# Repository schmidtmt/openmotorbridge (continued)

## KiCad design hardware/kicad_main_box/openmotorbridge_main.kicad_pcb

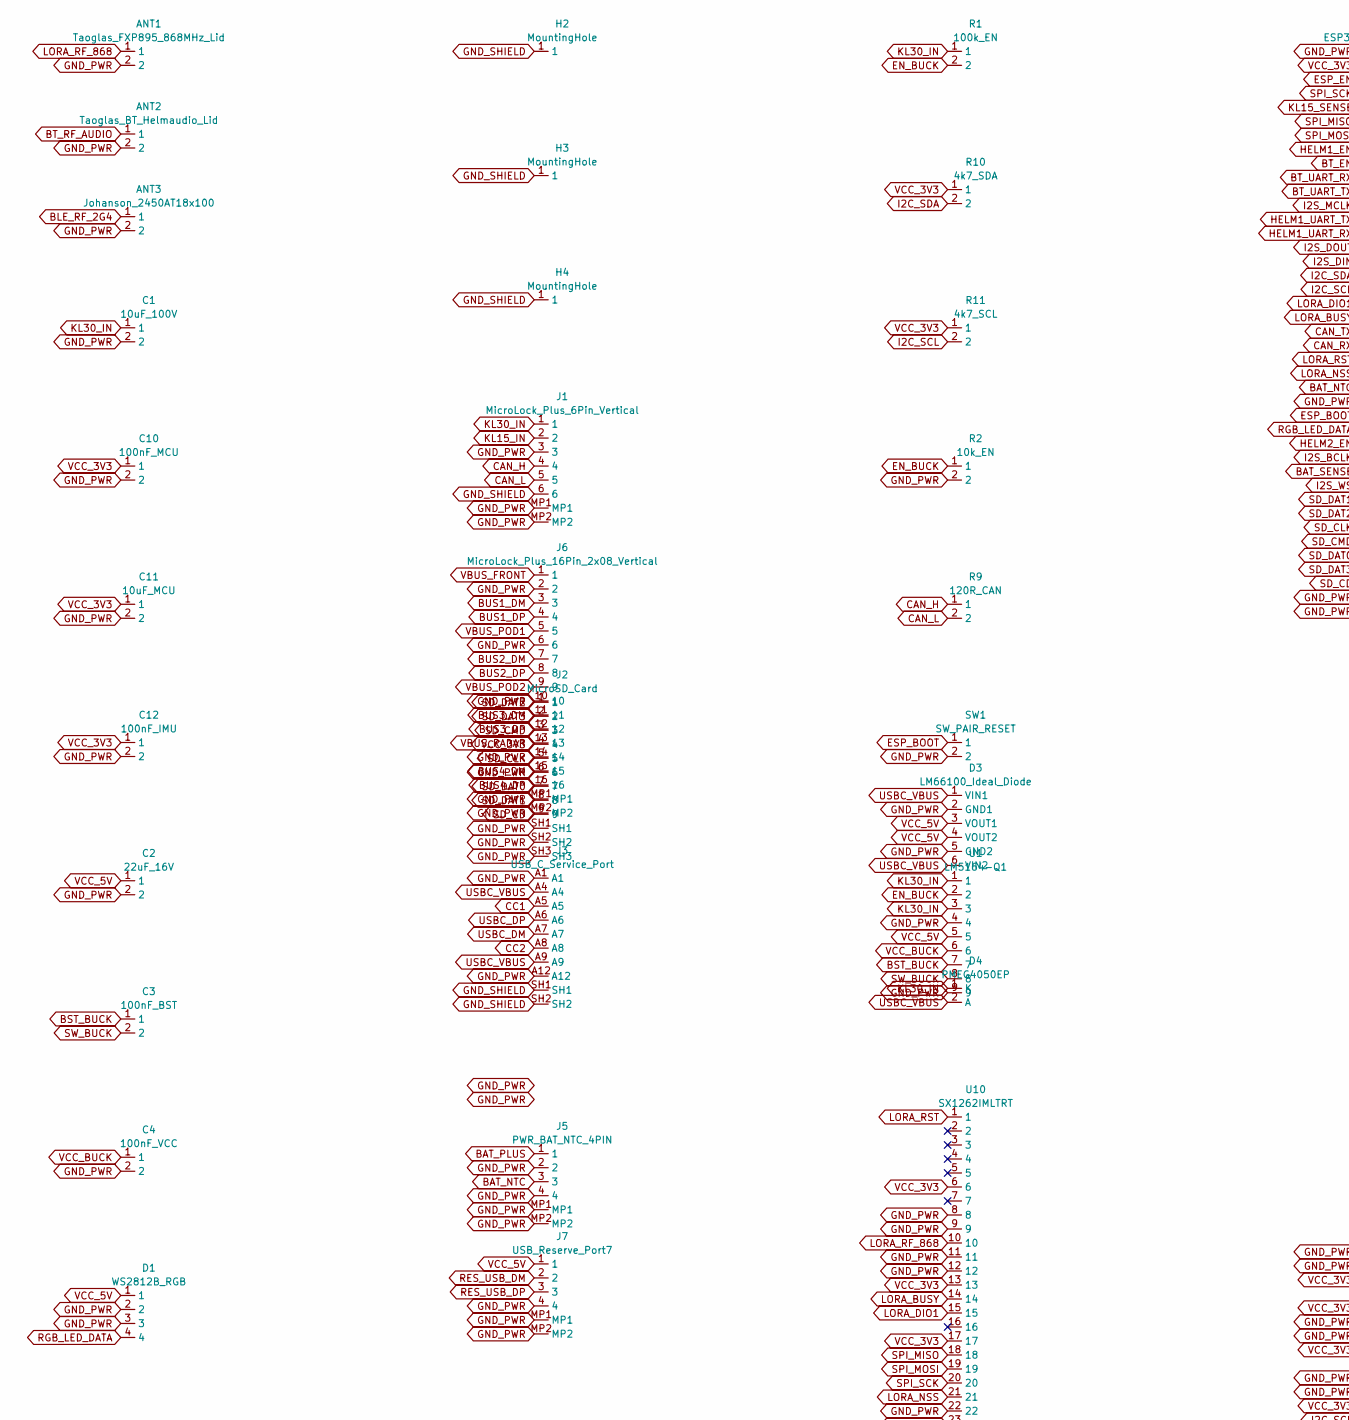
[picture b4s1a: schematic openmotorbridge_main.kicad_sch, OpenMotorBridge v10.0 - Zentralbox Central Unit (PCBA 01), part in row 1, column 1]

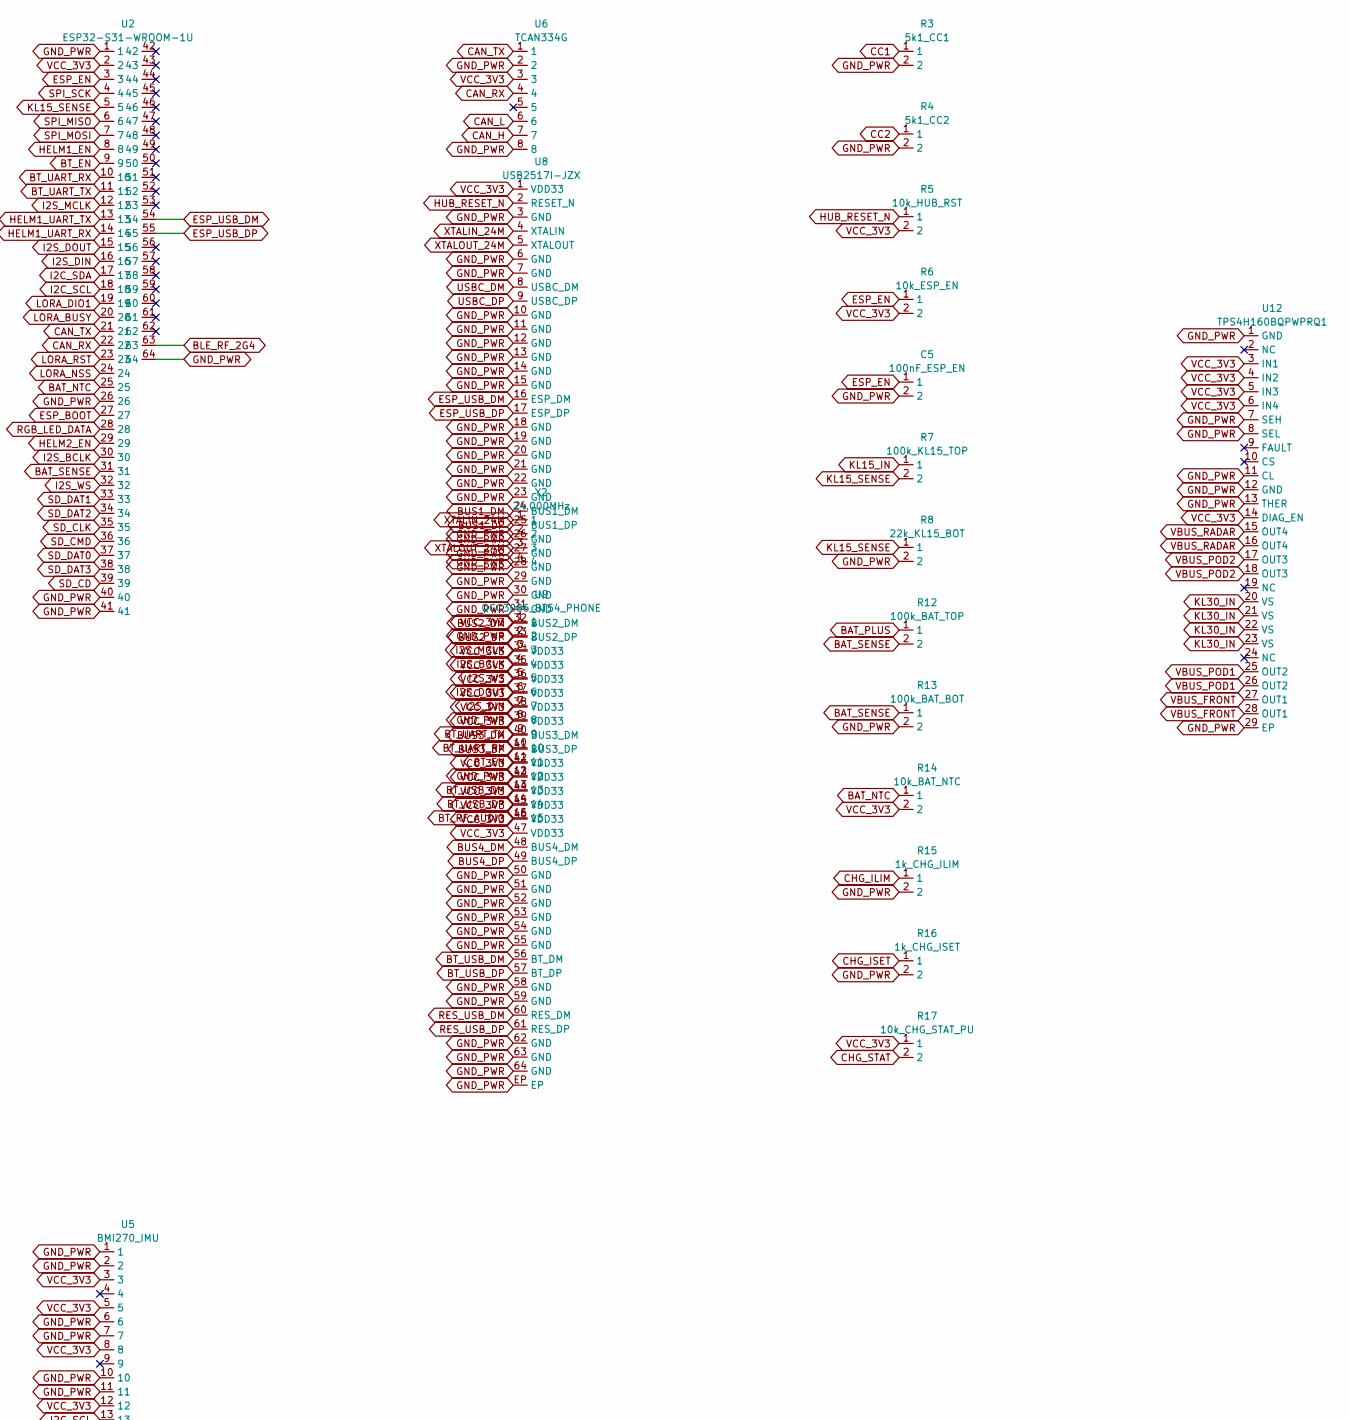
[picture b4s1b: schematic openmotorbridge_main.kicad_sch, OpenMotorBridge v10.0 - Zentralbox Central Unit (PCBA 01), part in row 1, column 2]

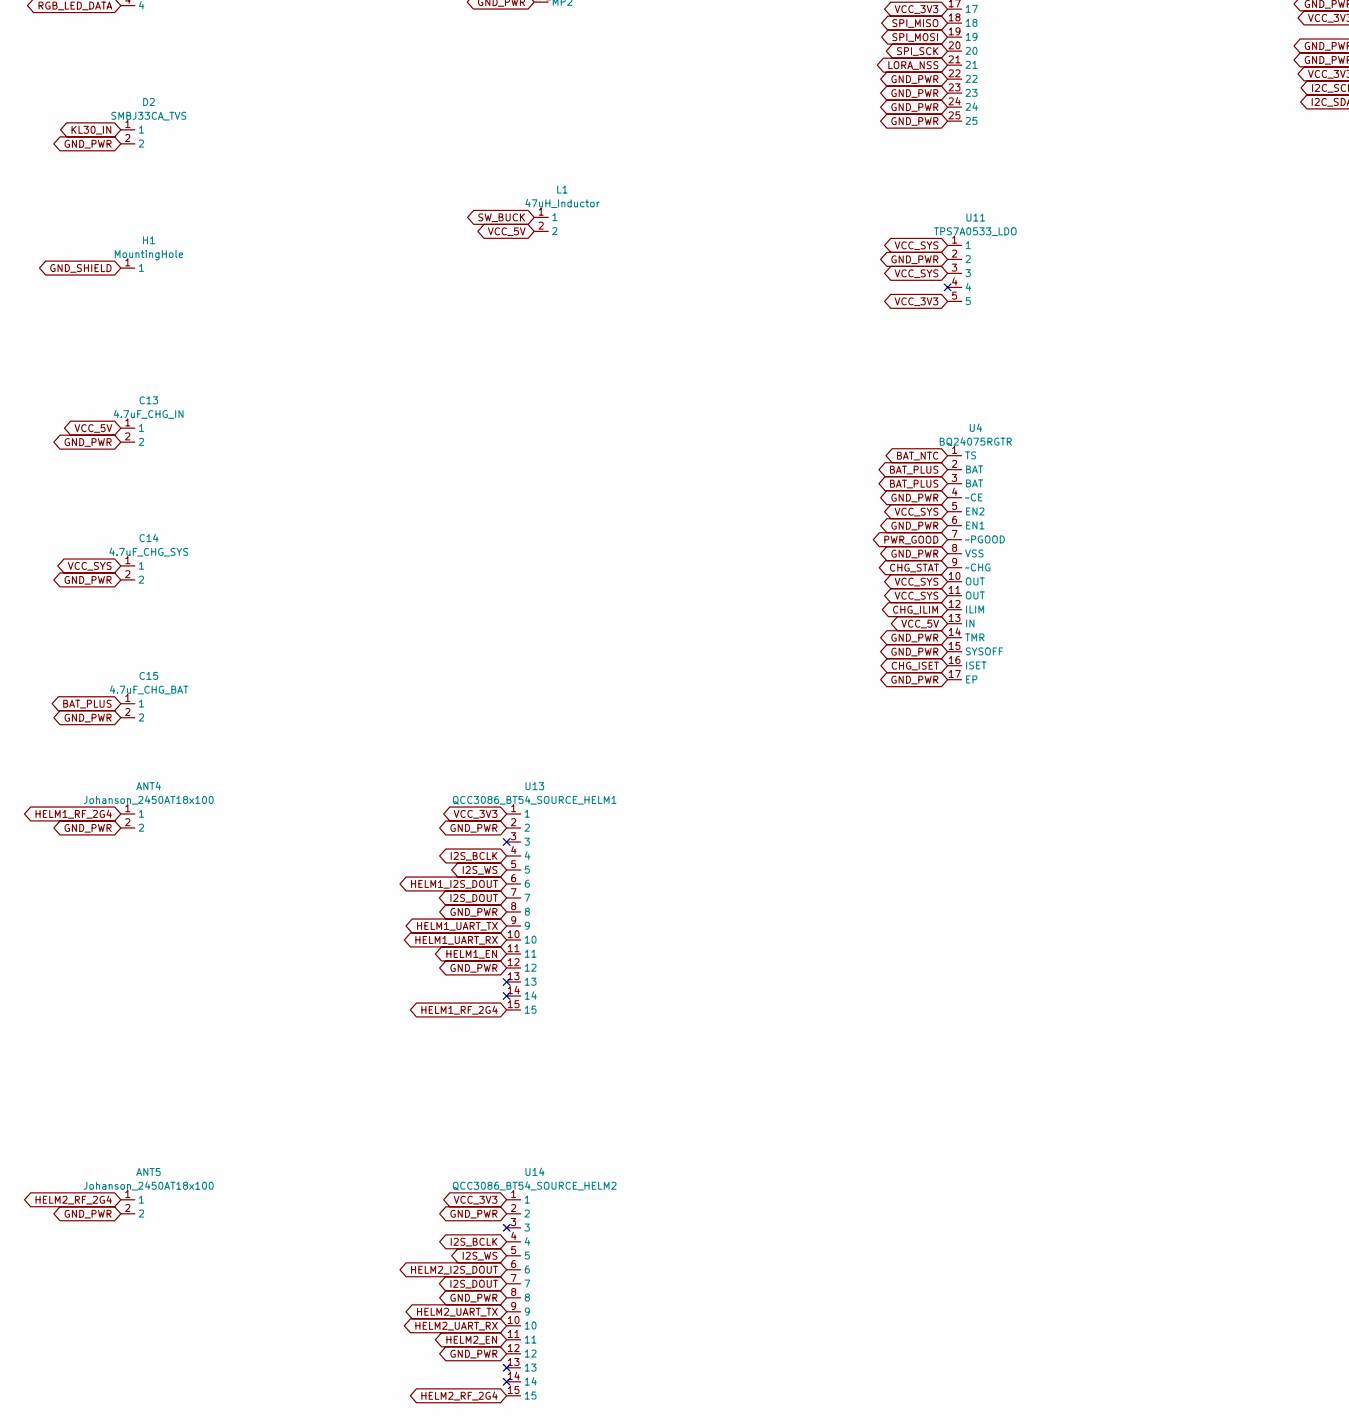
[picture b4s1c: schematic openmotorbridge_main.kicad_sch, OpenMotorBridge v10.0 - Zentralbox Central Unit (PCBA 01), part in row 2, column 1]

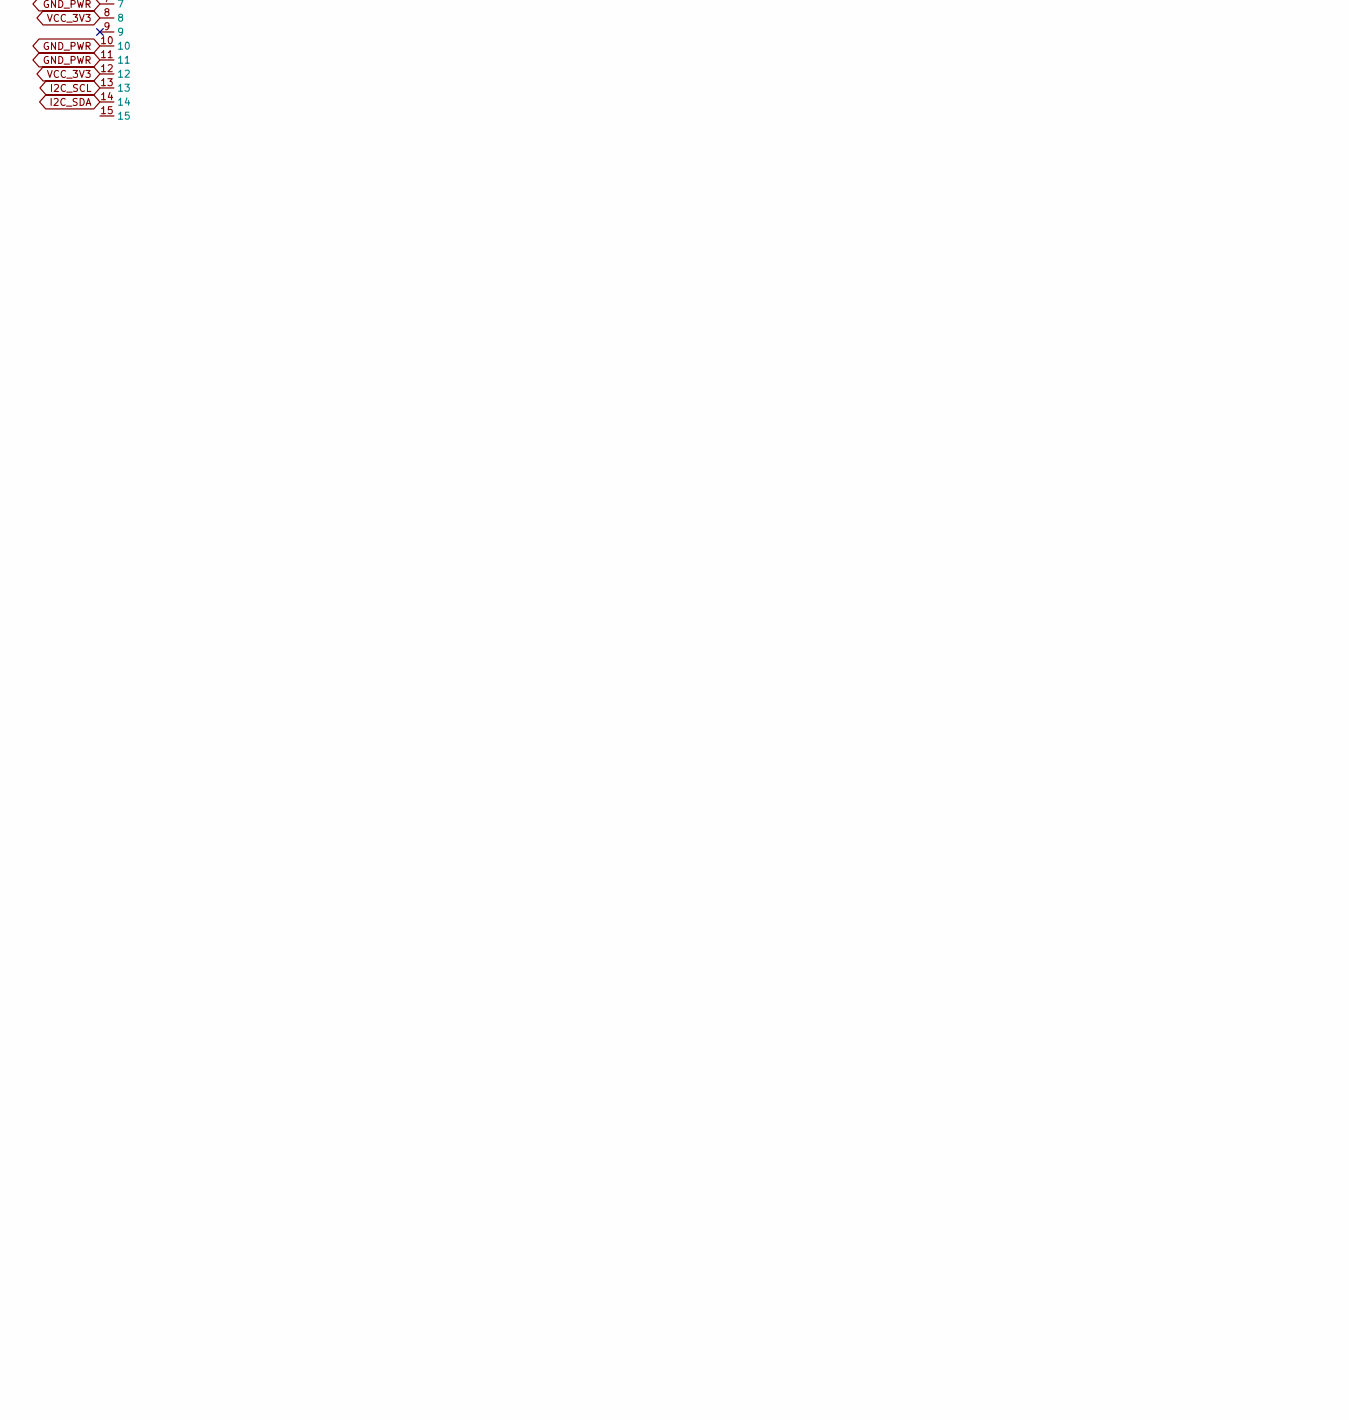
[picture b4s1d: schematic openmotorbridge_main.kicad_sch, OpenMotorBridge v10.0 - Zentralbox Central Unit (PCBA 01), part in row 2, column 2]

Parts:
ANT1: Taoglas_FXP895_868MHz_Lid; U.FL_Hirose_U.FL-R-SMT-1_Vertical
ANT2: Taoglas_BT_Helmaudio_Lid; U.FL_Hirose_U.FL-R-SMT-1_Vertical
ANT3, ANT4, ANT5: Johanson_2450AT18x100
C1: 10uF_100V; C_0805_2012Metric
C2: 22uF_16V; C_0805_2012Metric
C3: 100nF_BST; C_0603_1608Metric
C4: 100nF_VCC; C_0603_1608Metric
C5: 100nF_ESP_EN; C_0603_1608Metric
C10: 100nF_MCU; C_0603_1608Metric
C11: 10uF_MCU; C_0805_2012Metric
C12: 100nF_IMU; C_0603_1608Metric
C13: 4.7uF_CHG_IN; C_0603_1608Metric
C14: 4.7uF_CHG_SYS; C_0603_1608Metric
C15: 4.7uF_CHG_BAT; C_0603_1608Metric
D1: WS2812B_RGB; LED_WS2812B-2020
D2: SMBJ33CA_TVS; D_SMB
D3: LM66100_Ideal_Diode; SOT-23-6
D4: PMEG4050EP; D_SOD-128
H1, H2, H3, H4: MountingHole; MountingHole_3.2mm_M3_Pad_Via
J1: MicroLock_Plus_6Pin_Vertical; Molex_Micro-Lock_Plus_505568-0671_1x06_P1.25mm_Vertical
J2: MicroSD_Card; microSD_HC_Hirose_DM3D-SF
J3: USB_C_Service_Port; USB_C_Receptacle_HRO_TYPE-C-31-M-12_16P
J5: PWR_BAT_NTC_4PIN; Molex_Micro-Lock_Plus_505568-0471_1x04_P1.25mm_Vertical
J6: MicroLock_Plus_16Pin_2x08_Vertical; Molex_Micro-Lock_Plus_505433-1671_2x08_P1.25mm_Vertical
J7: USB_Reserve_Port7; Molex_Micro-Lock_Plus_505568-0471_1x04_P1.25mm_Vertical
L1: 47uH_Inductor; L_Sunlord_MWSA1206S-470
R1: 100k_EN; R_0603_1608Metric
R2: 10k_EN; R_0603_1608Metric
R3: 5k1_CC1; R_0603_1608Metric
R4: 5k1_CC2; R_0603_1608Metric
R5: 10k_HUB_RST; R_0603_1608Metric
R6: 10k_ESP_EN; R_0603_1608Metric
R7: 100k_KL15_TOP; R_0603_1608Metric
R8: 22k_KL15_BOT; R_0603_1608Metric
R9: 120R_CAN; R_0603_1608Metric
R10: 4k7_SDA; R_0603_1608Metric
R11: 4k7_SCL; R_0603_1608Metric
R12: 100k_BAT_TOP; R_0603_1608Metric
R13: 100k_BAT_BOT; R_0603_1608Metric
R14: 10k_BAT_NTC; R_0603_1608Metric
R15: 1k_CHG_ILIM; R_0603_1608Metric
R16: 1k_CHG_ISET; R_0603_1608Metric
R17: 10k_CHG_STAT_PU; R_0603_1608Metric
SW1: SW_PAIR_RESET; SW_Push_SPST_NO_Alps_SKRK
U1: LM5164-Q1; SOIC-8-1EP_3.9x4.9mm_P1.27mm_EP2.41x3.3mm
U2: ESP32-S31-WROOM-1U
U4: BQ24075RGTR; VQFN-16-1EP_3x3mm_P0.5mm_EP1.8x1.8mm
U5: BMI270_IMU; LGA-14_2.5x3mm_P0.5mm
U6: TCAN334G; SOIC-8_3.9x4.9mm_P1.27mm
U8: USB2517I-JZX; QFN-64-1EP_9x9mm_P0.5mm_EP7.15x7.15mm
U9: QCC3086_BT54_PHONE; Qualcomm_QCC3086_Module
U10: SX1262IMLTRT; QFN-24-1EP_4x4mm_P0.5mm_EP2.8x2.8mm
U11: TPS7A0533_LDO; SOT-23-5
U12: TPS4H160BQPWPRQ1; HTSSOP-28-1EP_4.4x9.7mm_P0.65mm_EP3.4x9.5mm_Mask2.4x6.17mm_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
U13: QCC3086_BT54_SOURCE_HELM1; Qualcomm_QCC3086_Module
U14: QCC3086_BT54_SOURCE_HELM2; Qualcomm_QCC3086_Module
Y2: 24.000MHz; Crystal_SMD_2016-4Pin_2.0x1.6mm

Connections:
BAT_NTC: J5.3, R14.1, U2.25, U4.1 (TS)
BAT_PLUS: C15.1, J5.1, R12.1, U4.2 (BAT), U4.3 (BAT)
BAT_SENSE: R12.2, R13.1, U2.31
BLE_RF_2G4: ANT3.1, U2.63
BST_BUCK: C3.1, U1.7
BT_EN: U2.9, U9.11
BT_RF_AUDIO: ANT2.1, U9.15
BT_UART_RX: U2.10, U9.10
BT_UART_TX: U2.11, U9.9
BT_USB_DM: U8.56 (BT_DM), U9.13
BT_USB_DP: U8.57 (BT_DP), U9.14
BUS1_DM: J6.3, U8.24 (BUS1_DM)
BUS1_DP: J6.4, U8.25 (BUS1_DP)
BUS2_DM: J6.7, U8.32 (BUS2_DM)
BUS2_DP: J6.8, U8.33 (BUS2_DP)
BUS3_DM: J6.11, U8.40 (BUS3_DM)
BUS3_DP: J6.12, U8.41 (BUS3_DP)
BUS4_DM: J6.15, U8.48 (BUS4_DM)
BUS4_DP: J6.16, U8.49 (BUS4_DP)
CAN_H: J1.4, R9.1, U6.7
CAN_L: J1.5, R9.2, U6.6
CAN_RX: U2.22, U6.4
CAN_TX: U2.21, U6.1
CC1: J3.A5, R3.1
CC2: J3.A8, R4.1
CHG_ILIM: R15.1, U4.12 (ILIM)
CHG_ISET: R16.1, U4.16 (ISET)
CHG_STAT: R17.2, U4.9 (~CHG)
EN_BUCK: R1.2, R2.1, U1.2
ESP_BOOT: SW1.1, U2.27
ESP_EN: C5.1, R6.1, U2.3
ESP_USB_DM: U2.54, U8.16 (ESP_DM)
ESP_USB_DP: U2.55, U8.17 (ESP_DP)
GND_PWR: ANT1.2, ANT2.2, ANT3.2, ANT4.2, ANT5.2, C1.2, C2.2, C4.2, C5.2, C10.2, C11.2, C12.2, C13.2, C14.2, C15.2, D1.2, D1.3, D2.2, D3.2 (GND1), D3.5 (GND2), J1.3, J1.MP1, J1.MP2, J2.6, J2.SH1, J2.SH2, J2.SH3, J3.A1, J3.A12, J5.2, J5.4, J5.MP1, J5.MP2, J6.2, J6.6, J6.10, J6.14, J6.MP1, J6.MP2, J7.4, J7.MP1, J7.MP2, R2.2, R3.2, R4.2, R8.2, R13.2, R15.2, R16.2, SW1.2, U1.4, U1.9, U2.1, U2.26, U2.40, U2.41, U2.64, U4.4 (~CE), U4.6 (EN1), U4.8 (VSS), U4.14 (TMR), U4.15 (SYSOFF), U4.17 (EP), U5.1, U5.2, U5.6, U5.7, U5.10, U5.11, U6.2, U6.8, U8.3 (GND), U8.6 (GND), U8.7 (GND), U8.10 (GND), U8.11 (GND), U8.12 (GND), U8.13 (GND), U8.14 (GND), U8.15 (GND), U8.18 (GND), U8.19 (GND), U8.20 (GND), U8.21 (GND), U8.22 (GND), U8.23 (GND), U8.26 (GND), U8.27 (GND), U8.28 (GND), U8.29 (GND), U8.30 (GND), U8.31 (GND), U8.50 (GND), U8.51 (GND), U8.52 (GND), U8.53 (GND), U8.54 (GND), U8.55 (GND), U8.58 (GND), U8.59 (GND), U8.62 (GND), U8.63 (GND), U8.64 (GND), U8.EP, U9.2, U9.8, U9.12, U10.8, U10.9, U10.11, U10.12, U10.22, U10.23, U10.24, U10.25, U11.2, U12.1 (GND), U12.7 (SEH), U12.8 (SEL), U12.11 (CL), U12.12 (GND), U12.13 (THER), U12.29 (EP), U13.2, U13.8, U13.12, U14.2, U14.8, U14.12, Y2.2, Y2.4
GND_SHIELD: H1.1 (1_1), H2.1 (1_1), H3.1 (1_1), H4.1 (1_1), J1.6, J3.SH1, J3.SH2
HELM1_EN: U2.8, U13.11
HELM1_I2S_DOUT: U13.6
HELM1_RF_2G4: ANT4.1, U13.15
HELM1_UART_RX: U2.14, U13.10
HELM1_UART_TX: U2.13, U13.9
HELM2_EN: U2.29, U14.11
HELM2_I2S_DOUT: U14.6
HELM2_RF_2G4: ANT5.1, U14.15
HELM2_UART_RX: U14.10
HELM2_UART_TX: U14.9
HUB_RESET_N: R5.1, U8.2 (RESET_N)
I2C_SCL: R11.2, U2.18, U5.13
I2C_SDA: R10.2, U2.17, U5.14
I2S_BCLK: U2.30, U9.4, U13.4, U14.4
I2S_DIN: U2.16, U9.7
I2S_DOUT: U2.15, U9.6, U13.7, U14.7
I2S_MCLK: U2.12, U9.3
I2S_WS: U2.32, U9.5, U13.5, U14.5
KL15_IN: J1.2, R7.1
KL15_SENSE: R7.2, R8.1, U2.5
KL30_IN: C1.1, D2.1, D4.1 (K), J1.1, R1.1, U1.1, U1.3, U12.20 (VS), U12.21 (VS), U12.22 (VS), U12.23 (VS)
LORA_BUSY: U2.20, U10.14
LORA_DIO1: U2.19, U10.15
LORA_NSS: U2.24, U10.21
LORA_RF_868: ANT1.1, U10.10
LORA_RST: U2.23, U10.1
PWR_GOOD: U4.7 (~PGOOD)
RES_USB_DM: J7.2, U8.60 (RES_DM)
RES_USB_DP: J7.3, U8.61 (RES_DP)
RGB_LED_DATA: D1.4, U2.28
SD_CD: J2.9, U2.39
SD_CLK: J2.5, U2.35
SD_CMD: J2.3, U2.36
SD_DAT0: J2.7, U2.37
SD_DAT1: J2.8, U2.33
SD_DAT2: J2.1, U2.34
SD_DAT3: J2.2, U2.38
SPI_MISO: U2.6, U10.18
SPI_MOSI: U2.7, U10.19
SPI_SCK: U2.4, U10.20
SW_BUCK: C3.2, L1.1, U1.8
USBC_DM: J3.A7, U8.8 (USBC_DM)
USBC_DP: J3.A6, U8.9 (USBC_DP)
USBC_VBUS: D3.1 (VIN1), D3.6 (VIN2), D4.2 (A), J3.A4, J3.A9
VBUS_FRONT: J6.1, U12.27 (OUT1), U12.28 (OUT1)
VBUS_POD1: J6.5, U12.25 (OUT2), U12.26 (OUT2)
VBUS_POD2: J6.9, U12.17 (OUT3), U12.18 (OUT3)
VBUS_RADAR: J6.13, U12.15 (OUT4), U12.16 (OUT4)
VCC_3V3: C10.1, C11.1, C12.1, J2.4, R5.2, R6.2, R10.1, R11.1, R14.2, R17.1, U2.2, U5.3, U5.5, U5.8, U5.12, U6.3, U8.1 (VDD33), U8.34 (VDD33), U8.35 (VDD33), U8.36 (VDD33), U8.37 (VDD33), U8.38 (VDD33), U8.39 (VDD33), U8.42 (VDD33), U8.43 (VDD33), U8.44 (VDD33), U8.45 (VDD33), U8.46 (VDD33), U8.47 (VDD33), U9.1, U10.6, U10.13, U10.17, U11.5, U12.3 (IN1), U12.4 (IN2), U12.5 (IN3), U12.6 (IN4), U12.14 (DIAG_EN), U13.1, U14.1
VCC_5V: C2.1, C13.1, D1.1, D3.3 (VOUT1), D3.4 (VOUT2), J7.1, L1.2, U1.5, U4.13 (IN)
VCC_BUCK: C4.1, U1.6
VCC_SYS: C14.1, U4.5 (EN2), U4.10 (OUT), U4.11 (OUT), U11.1, U11.3
XTALIN_24M: U8.4 (XTALIN), Y2.1
XTALOUT_24M: U8.5 (XTALOUT), Y2.3

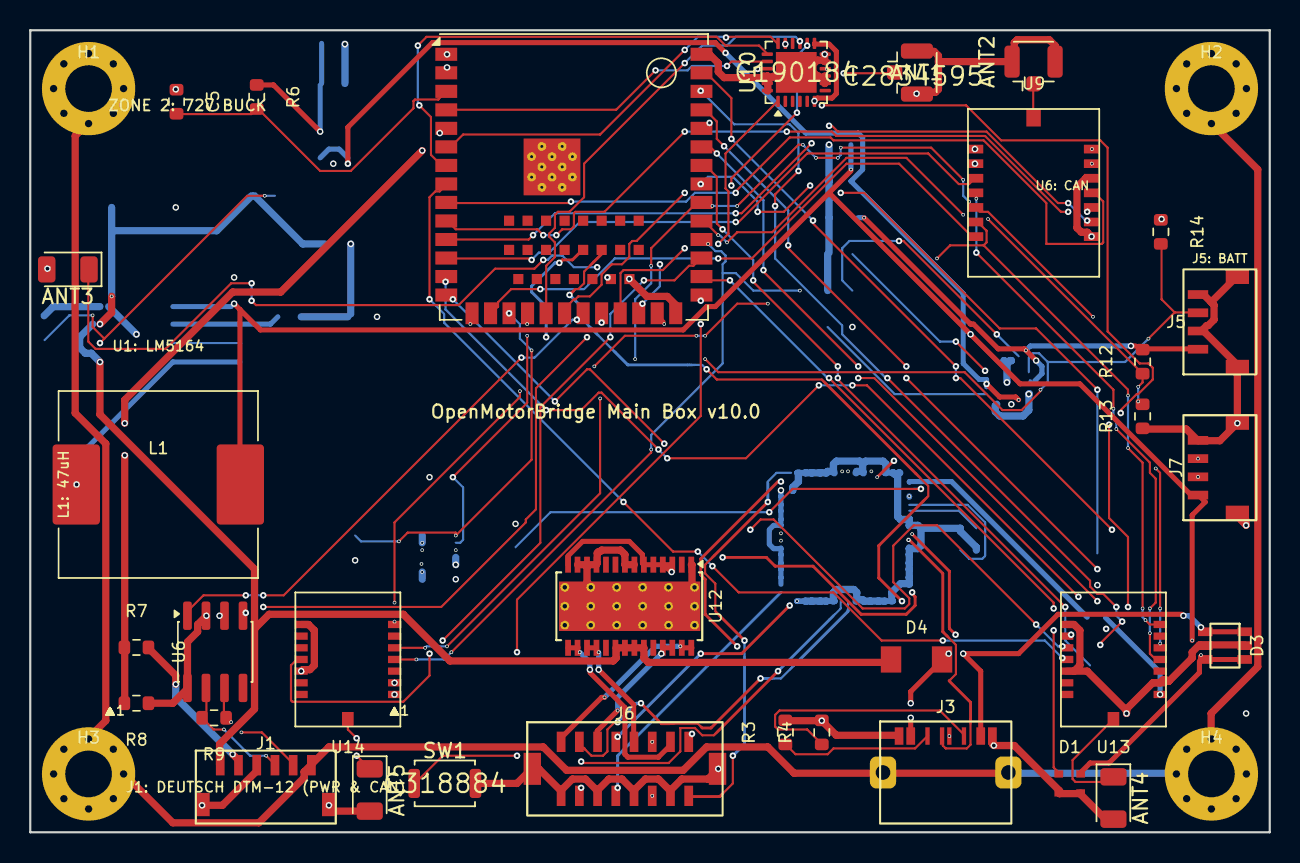
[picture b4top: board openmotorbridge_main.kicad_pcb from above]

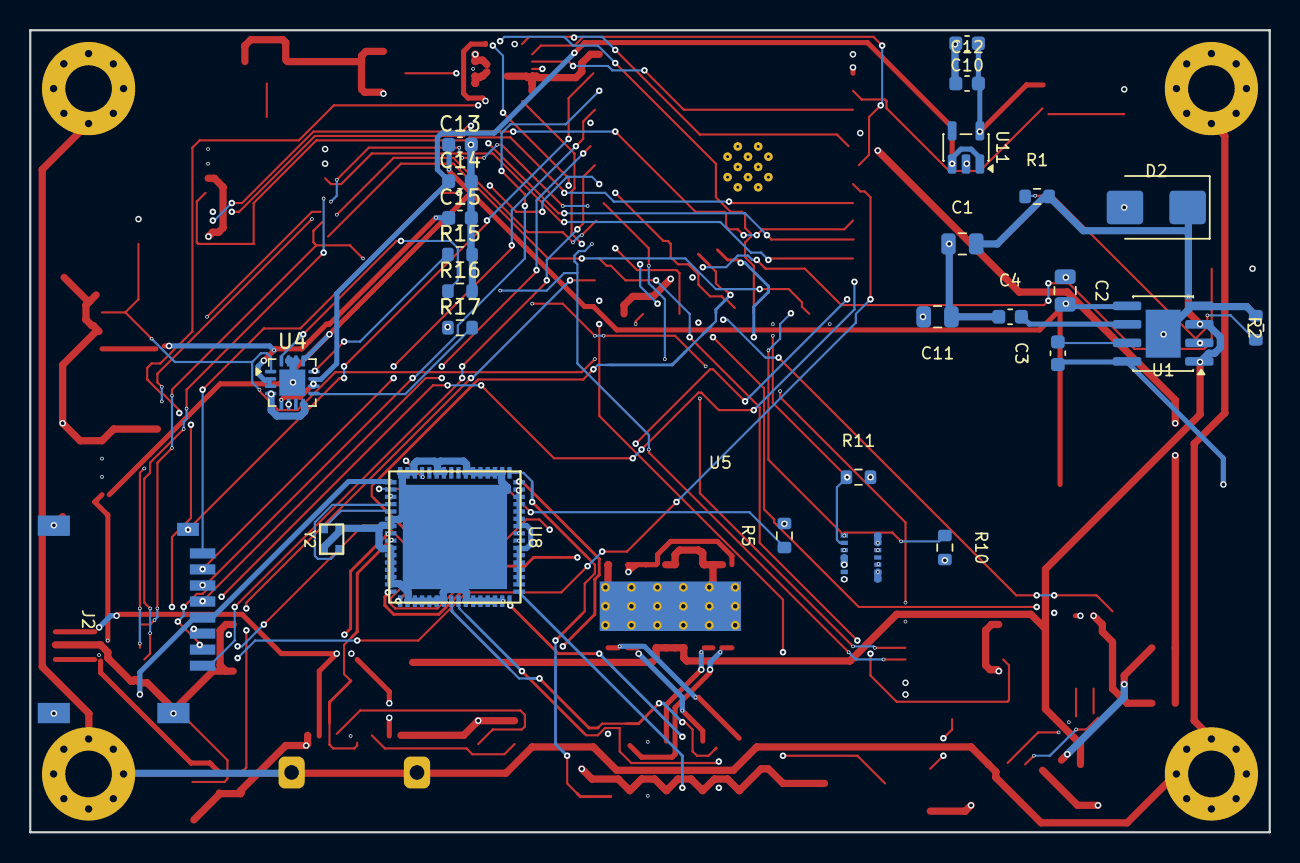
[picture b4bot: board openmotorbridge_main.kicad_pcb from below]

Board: 4 copper layers, 85.0 x 55.0 mm, 62 parts (26 on the bottom side), 84 nets.

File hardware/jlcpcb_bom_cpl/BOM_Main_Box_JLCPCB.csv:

Designator,Comment,Footprint,LCSC Part #,Quantity
ANT1,Taoglas_FXP895_868MHz_Lid,U.FL_Hirose_U.FL-R-SMT-1_Vertical,C2834595,1
ANT2,Taoglas_FXUWB10_6.5GHz_Ch5_Floor,U.FL_Hirose_U.FL-R-SMT-1_Vertical,C2834595,1
C1,10uF_100V,Capacitor_SMD:C_0805_2012Metric,,1
C10,100nF_MCU,Capacitor_SMD:C_0603_1608Metric,,1
C11,10uF_MCU,Capacitor_SMD:C_0805_2012Metric,,1
C12,100nF_IMU,Capacitor_SMD:C_0603_1608Metric,,1
C2,22uF_16V,Capacitor_SMD:C_0805_2012Metric,,1
C3,100nF_BST,Capacitor_SMD:C_0603_1608Metric,,1
C4,100nF_VCC,Capacitor_SMD:C_0603_1608Metric,,1
C6,1uF_POD1,Capacitor_SMD:C_0603_1608Metric,,1
C7,1uF_POD2,Capacitor_SMD:C_0603_1608Metric,,1
D1,WS2812B_RGB,LED_SMD:LED_WS2812B-2020,,1
D2,SMBJ33CA_TVS,Diode_SMD:D_SMB,,1
"H1, H2, H3, H4",,MountingHole:MountingHole_3.2mm_M3_Pad_Via,,4
J1,DEUTSCH_DTM12_HEADER,Connector_IDC:IDC-Header_2x13_P2.54mm_Vertical,C2934175,1
J2,MicroSD_Card,Connector_Card:microSD_HC_Molex_47571-0001,,1
J3,USB2_IDC_HEADER_9PIN,Connector_IDC:IDC-Header_2x05_P2.54mm_Vertical,,1
J4,RGB_LED_3PIN,Connector_JST:JST_PH_B3B-PH-K_1x03_P2.00mm_Vertical,,1
J5,PWR_BAT_NTC_4PIN,Connector_JST:JST_PH_B4B-PH-K_1x04_P2.00mm_Vertical,,1
L1,47uH_Inductor,Inductor_SMD:L_Sunlord_MWSA1206S-470,,1
R1,100k_EN,Resistor_SMD:R_0603_1608Metric,,1
R10,4k7_SDA,Resistor_SMD:R_0603_1608Metric,,1
R11,4k7_SCL,Resistor_SMD:R_0603_1608Metric,,1
R2,10k_EN,Resistor_SMD:R_0603_1608Metric,,1
R5,600R_POD1,Resistor_SMD:R_0603_1608Metric,,1
R6,600R_POD2,Resistor_SMD:R_0603_1608Metric,,1
R9,120R_CAN,Resistor_SMD:R_0603_1608Metric,,1
SW1,SW_PAIR_RESET,SW_Push_SPST_NO_Alps_SKRK,C318884,1
U1,LM5164-Q1,Package_SO:SOIC-8-1EP_3.9x4.9mm_P1.27mm_EP2.41x3.3mm,,1
U2,ESP32-S3-WROOM-1U-N16R8,ESP32-S3-WROOM-1U,,1
U3,ES8388_Codec,Package_DFN_QFN:QFN-28-1EP_4x4mm_P0.4mm_EP2.4x2.4mm,,1
U5,BMI270_IMU,Package_LGA:LGA-14_2.5x3mm_P0.5mm,,1
U6,TCAN334G,Package_SO:SOIC-8_3.9x4.9mm_P1.27mm,,1
U7,SX1262IMLTRT,QFN-24-1EP_4x4mm_P0.5mm_EP2.8x2.8mm,C190184,1
U8,DW3110,QFN-16-1EP_3x3mm_P0.5mm_EP1.7x1.7mm_ThermalVias,C2934600,1
U9,TPS7A0533_LDO,Package_TO_SOT_SMD:SOT-23-5,,1

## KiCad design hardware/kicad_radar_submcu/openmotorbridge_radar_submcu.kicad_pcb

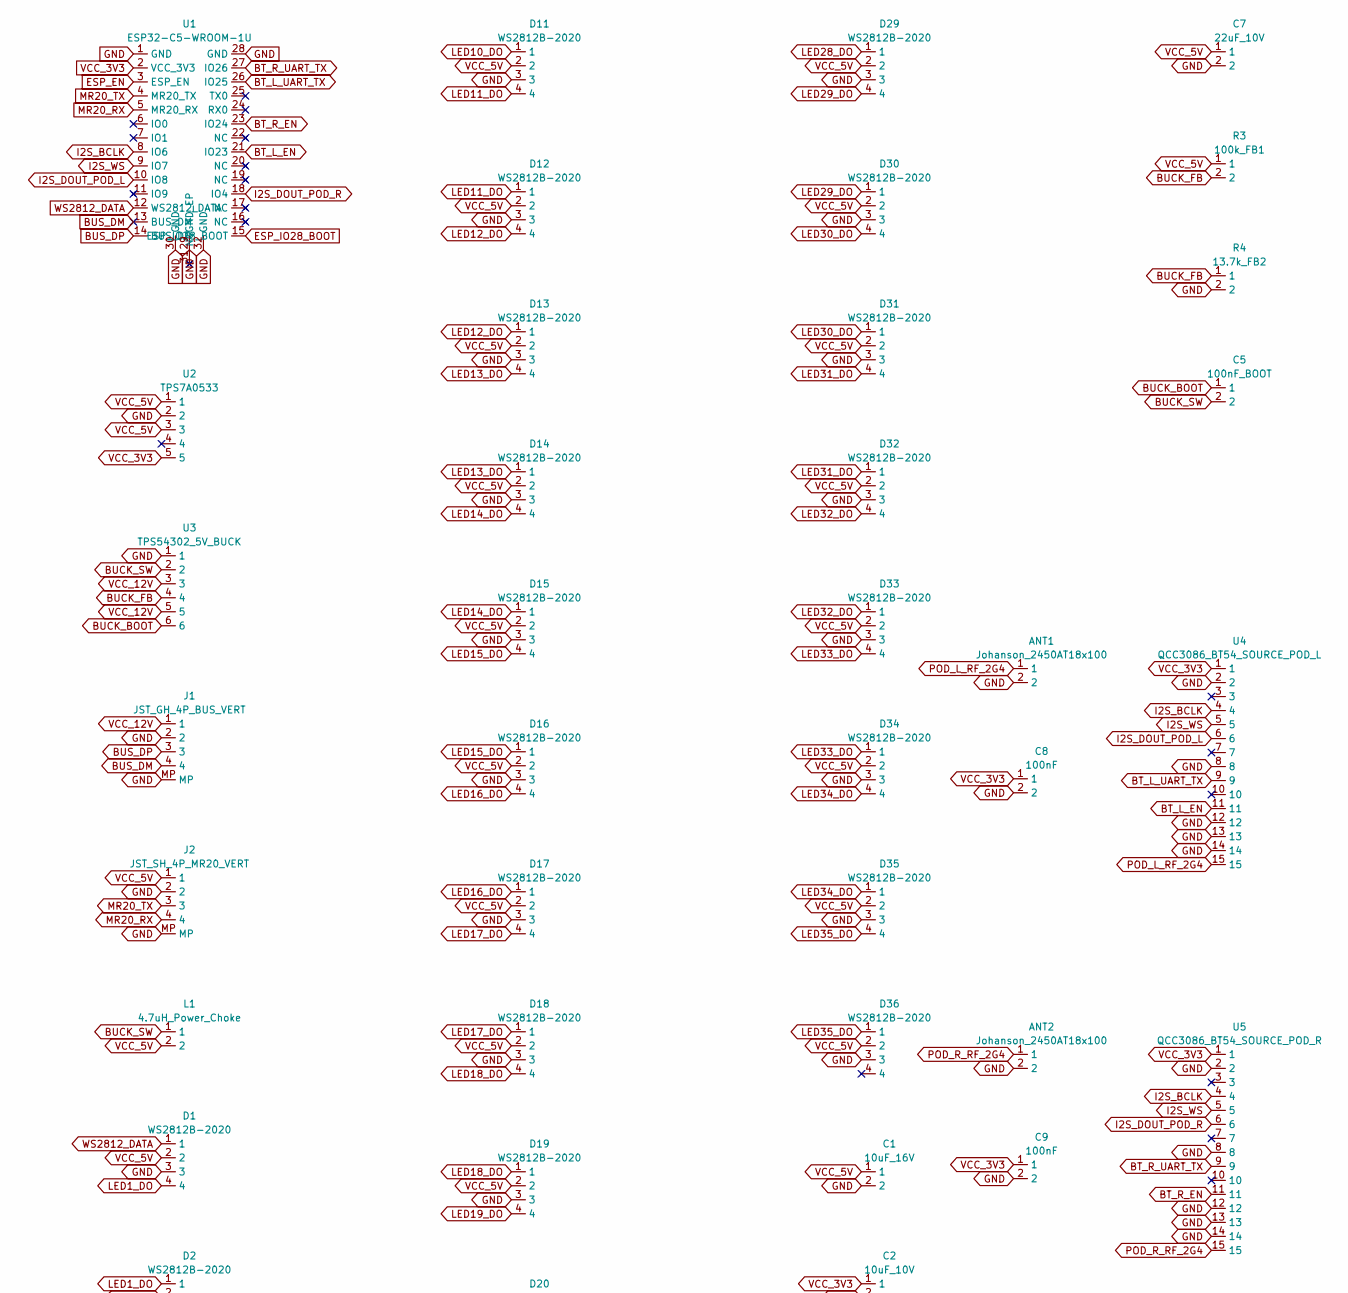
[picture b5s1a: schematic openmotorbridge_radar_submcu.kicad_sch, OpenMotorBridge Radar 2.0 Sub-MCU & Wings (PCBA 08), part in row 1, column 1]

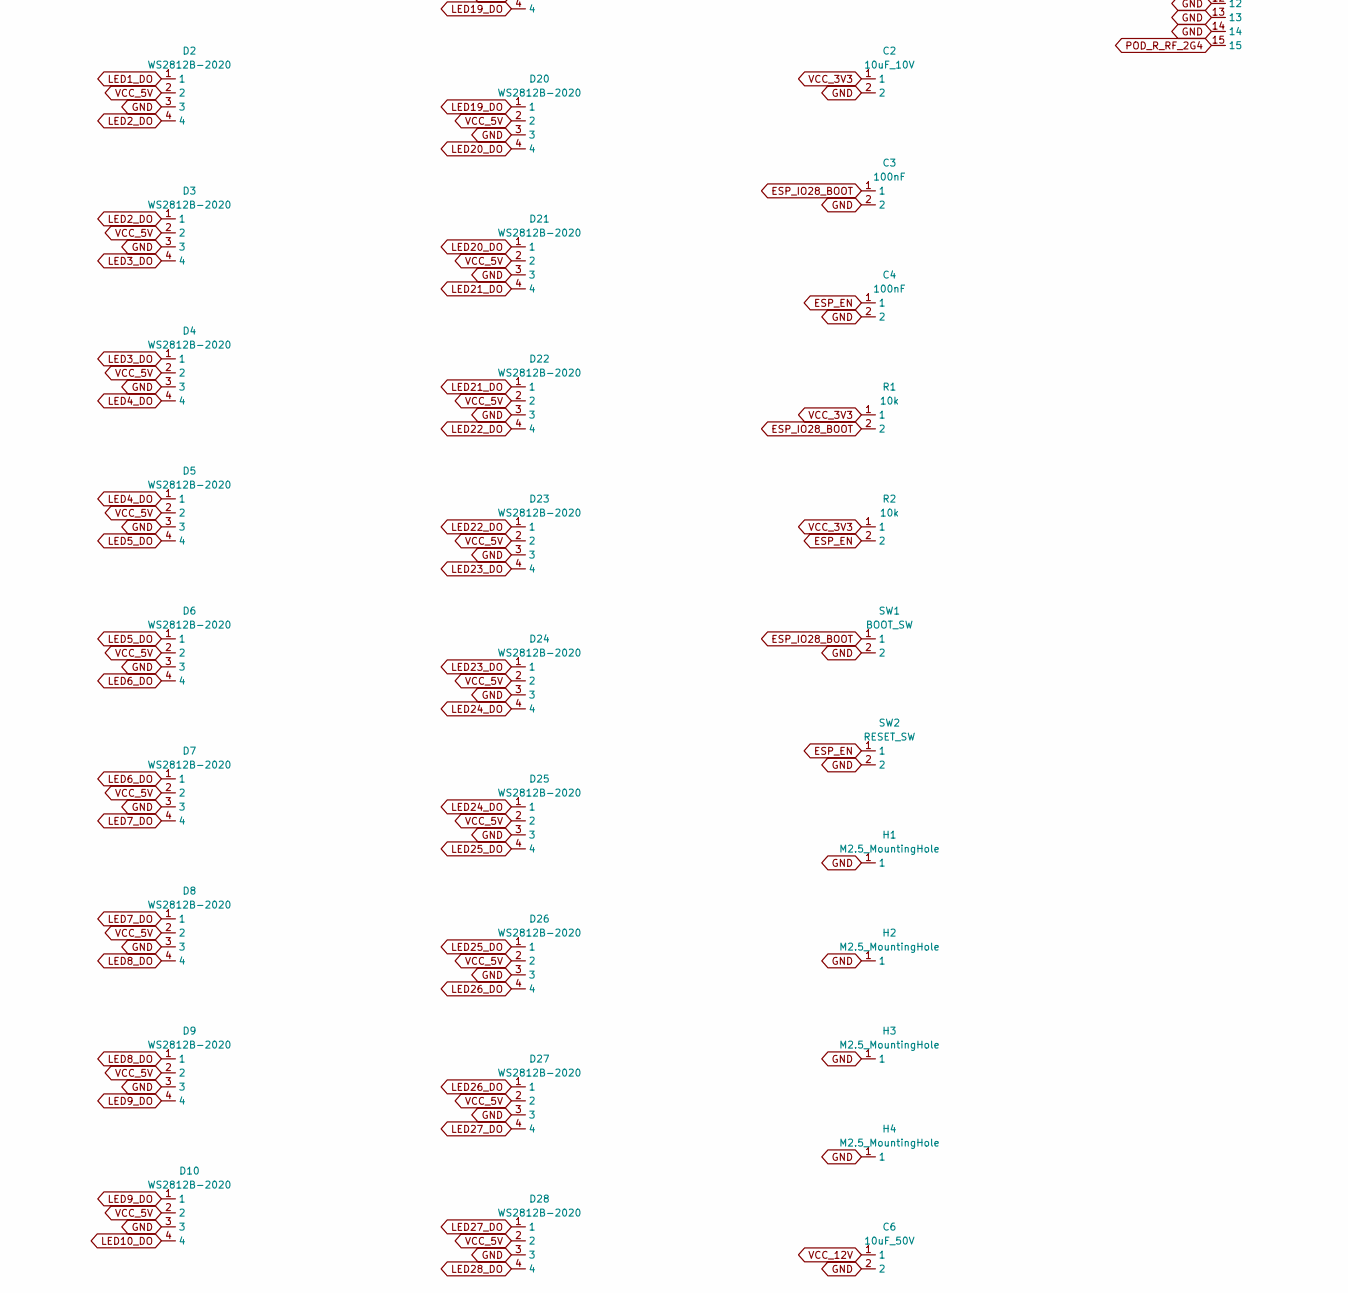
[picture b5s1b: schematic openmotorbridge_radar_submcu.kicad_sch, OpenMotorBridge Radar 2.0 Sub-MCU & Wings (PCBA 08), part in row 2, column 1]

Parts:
ANT1, ANT2: Johanson_2450AT18x100
C1: 10uF_16V; C_0805_2012Metric
C2: 10uF_10V; C_0805_2012Metric
C3, C4, C8, C9: 100nF; C_0603_1608Metric
C5: 100nF_BOOT; C_0603_1608Metric
C6: 10uF_50V; C_0805_2012Metric
C7: 22uF_10V; C_0805_2012Metric
D1, D2, D3, D4, D5, D6, D7, D8, D9, D10, D11, D12, D13, D14, D15, D16, D17, D18, D19, D20, D21, D22, D23, D24, D25, D26, D27, D28, D29, D30, D31, D32, D33, D34, D35, D36: WS2812B-2020; LED_WS2812B-2020_PLCC4_2.0x2.0mm
H1, H2, H3, H4: M2.5_MountingHole; MountingHole_2.7mm_M2.5_Pad
J1: JST_GH_4P_BUS_VERT; JST_GH_BM04B-GHS-TBT_1x04-1MP_P1.25mm_Vertical
J2: JST_SH_4P_MR20_VERT; JST_SH_BM04B-SRSS-TB_1x04-1MP_P1.00mm_Vertical
L1: 4.7uH_Power_Choke; L_Sunlord_MWSA1206S-4R7
R1, R2: 10k; R_0603_1608Metric
R3: 100k_FB1; R_0603_1608Metric
R4: 13.7k_FB2; R_0603_1608Metric
SW1: BOOT_SW; SW_Push_SPST_NO_Alps_SKRK
SW2: RESET_SW; SW_Push_SPST_NO_Alps_SKRK
U1: ESP32-C5-WROOM-1U
U2: TPS7A0533; SOT-23-5
U3: TPS54302_5V_BUCK; SOT-23-6
U4: QCC3086_BT54_SOURCE_POD_L; Qualcomm_QCC3086_Module
U5: QCC3086_BT54_SOURCE_POD_R; Qualcomm_QCC3086_Module

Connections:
BT_L_EN: U1.21 (IO23), U4.11
BT_L_UART_TX: U1.26 (IO25), U4.9
BT_R_EN: U1.23 (IO24), U5.11
BT_R_UART_TX: U1.27 (IO26), U5.9
BUCK_BOOT: C5.1, U3.6
BUCK_FB: R3.2, R4.1, U3.4
BUCK_SW: C5.2, L1.1, U3.2
BUS_DM: J1.4, U1.13 (BUS_DM)
BUS_DP: J1.3, U1.14 (BUS_DP)
ESP_EN: C4.1, R2.2, SW2.1, U1.3 (ESP_EN)
ESP_IO28_BOOT: C3.1, R1.2, SW1.1, U1.15 (ESP_IO28_BOOT)
GND: ANT1.2, ANT2.2, C1.2, C2.2, C3.2, C4.2, C6.2, C7.2, C8.2, C9.2, D1.3, D2.3, D3.3, D4.3, D5.3, D6.3, D7.3, D8.3, D9.3, D10.3, D11.3, D12.3, D13.3, D14.3, D15.3, D16.3, D17.3, D18.3, D19.3, D20.3, D21.3, D22.3, D23.3, D24.3, D25.3, D26.3, D27.3, D28.3, D29.3, D30.3, D31.3, D32.3, D33.3, D34.3, D35.3, D36.3, H1.1 (1_1), H2.1 (1_1), H3.1 (1_1), H4.1 (1_1), J1.2, J1.MP, J2.2, J2.MP, R4.2, SW1.2, SW2.2, U1.1 (GND), U1.28 (GND), U1.29 (GND_EP), U1.30 (GND), U1.32 (GND), U2.2, U3.1, U4.2, U4.8, U4.12, U4.13, U4.14, U5.2, U5.8, U5.12, U5.13, U5.14
I2S_BCLK: U1.8 (IO6), U4.4, U5.4
I2S_DOUT_POD_L: U1.10 (IO8), U4.6
I2S_DOUT_POD_R: U1.18 (IO4), U5.6
I2S_WS: U1.9 (IO7), U4.5, U5.5
LED1_DO: D1.4, D2.1
LED2_DO: D2.4, D3.1
LED3_DO: D3.4, D4.1
LED4_DO: D4.4, D5.1
LED5_DO: D5.4, D6.1
LED6_DO: D6.4, D7.1
LED7_DO: D7.4, D8.1
LED8_DO: D8.4, D9.1
LED9_DO: D9.4, D10.1
LED10_DO: D10.4, D11.1
LED11_DO: D11.4, D12.1
LED12_DO: D12.4, D13.1
LED13_DO: D13.4, D14.1
LED14_DO: D14.4, D15.1
LED15_DO: D15.4, D16.1
LED16_DO: D16.4, D17.1
LED17_DO: D17.4, D18.1
LED18_DO: D18.4, D19.1
LED19_DO: D19.4, D20.1
LED20_DO: D20.4, D21.1
LED21_DO: D21.4, D22.1
LED22_DO: D22.4, D23.1
LED23_DO: D23.4, D24.1
LED24_DO: D24.4, D25.1
LED25_DO: D25.4, D26.1
LED26_DO: D26.4, D27.1
LED27_DO: D27.4, D28.1
LED28_DO: D28.4, D29.1
LED29_DO: D29.4, D30.1
LED30_DO: D30.4, D31.1
LED31_DO: D31.4, D32.1
LED32_DO: D32.4, D33.1
LED33_DO: D33.4, D34.1
LED34_DO: D34.4, D35.1
LED35_DO: D35.4, D36.1
MR20_RX: J2.4, U1.5 (MR20_RX)
MR20_TX: J2.3, U1.4 (MR20_TX)
POD_L_RF_2G4: ANT1.1, U4.15
POD_R_RF_2G4: ANT2.1, U5.15
VCC_3V3: C2.1, C8.1, C9.1, R1.1, R2.1, U1.2 (VCC_3V3), U2.5, U4.1, U5.1
VCC_5V: C1.1, C7.1, D1.2, D2.2, D3.2, D4.2, D5.2, D6.2, D7.2, D8.2, D9.2, D10.2, D11.2, D12.2, D13.2, D14.2, D15.2, D16.2, D17.2, D18.2, D19.2, D20.2, D21.2, D22.2, D23.2, D24.2, D25.2, D26.2, D27.2, D28.2, D29.2, D30.2, D31.2, D32.2, D33.2, D34.2, D35.2, D36.2, J2.1, L1.2, R3.1, U2.1, U2.3
VCC_12V: C6.1, J1.1, U3.3, U3.5
WS2812_DATA: D1.1, U1.12 (WS2812_DATA)
